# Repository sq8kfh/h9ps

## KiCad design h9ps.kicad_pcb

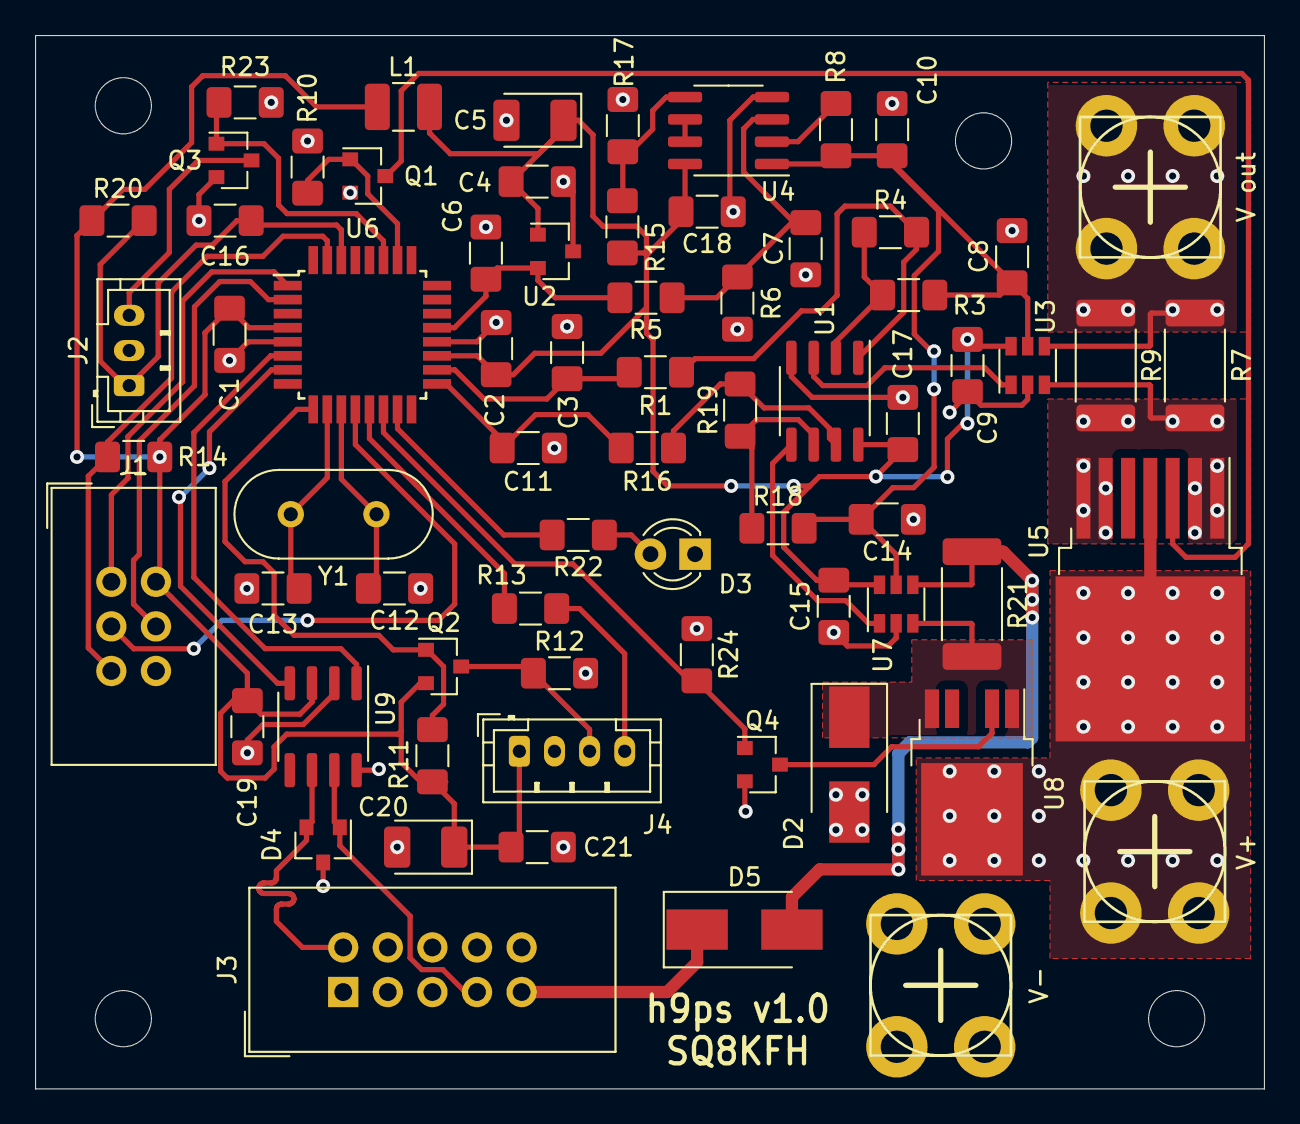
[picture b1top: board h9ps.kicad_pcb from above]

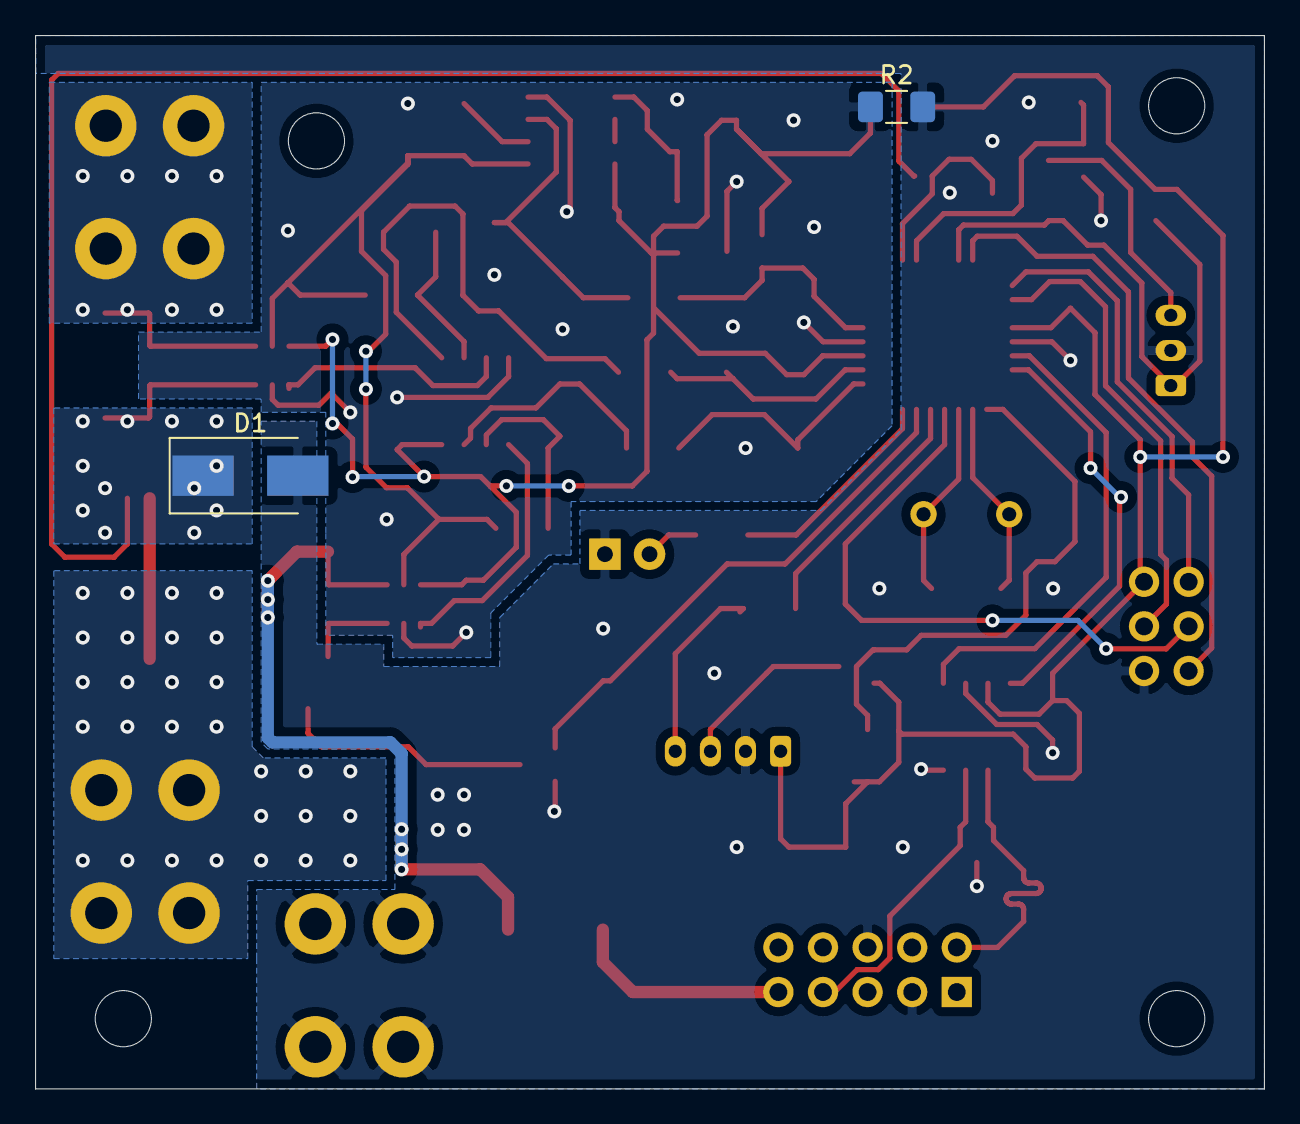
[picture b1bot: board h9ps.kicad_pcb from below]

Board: 2 copper layers, 70.0 x 60.0 mm, 73 parts (2 on the bottom side), 47 nets.

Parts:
 : MountingHole_3.2mm_M3
C1, C2, C3, C4, C7, C8, C9, C11, C14, C15, C16, C17, C18, C19, C21: 100n; C_1206_3216Metric_Pad1.42x1.75mm_HandSolder
C5, C20: 47uF; CP_EIA-3528-21_Kemet-B_Pad1.50x2.35mm_HandSolder
C6, C10: 1uF; C_1206_3216Metric_Pad1.42x1.75mm_HandSolder
C12, C13: 22p; C_1206_3216Metric_Pad1.42x1.75mm_HandSolder
D1, D2, D5: S1M; D_SMB_Handsoldering
D3: LED_Small_ALT; LED_D3.0mm
D4: NUP2105L; SOT-23
J1: AVR-ISP-6; IDC-Header_2x03_P2.54mm_Vertical
J2: Conn_01x03; JST_PH_B3B-PH-K_1x03_P2.00mm_Vertical
J3: DB9; IDC-Header_2x05_P2.54mm_Vertical
J4: Conn_01x04; JST_PH_B4B-PH-K_1x04_P2.00mm_Vertical
L1: 10uH; L_1210_3225Metric_Pad1.42x2.65mm_HandSolder
Q1, Q3, Q4: 2N7002; SOT-23
Q2: BSS84; SOT-23
R1, R13, R16: 100; R_1206_3216Metric_Pad1.42x1.75mm_HandSolder
R2, R4, R19: 0R; R_1206_3216Metric_Pad1.42x1.75mm_HandSolder
R3, R18: NN; R_1206_3216Metric_Pad1.42x1.75mm_HandSolder
R5, R6, R8, R10, R11, R12, R14, R15, R17, R20, R22, R23, R24: 10k; R_1206_3216Metric_Pad1.42x1.75mm_HandSolder
R7, R9: 0R003; R_2512_6332Metric_Pad1.52x3.35mm_HandSolder
R21: 0R3; R_2512_6332Metric_Pad1.52x3.35mm_HandSolder
U1, U4: TLC272; SOIC-8_3.9x4.9mm_P1.27mm
U2: MCP1541-TT; SOT-23
U3: INA181A3; SOT-23-6
U5: BTS50085-1TMA; TO-263-7_TabPin4
U6: ATmega16M1-AU; TQFP-32_7x7mm_P0.8mm
U7: INA181A1; SOT-23-6
U8: BTS443P; TO-252-4
U9: MCP2551-I-SN; SOIC-8_3.9x4.9mm_P1.27mm
V out: PWR_OUT; Screw_Terminal_M4
V+: VPP; Screw_Terminal_M4
V-: PWR_GND; Screw_Terminal_M4
Y1: 16MHz; Crystal_HC49-U_Vertical

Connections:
+5V: C1.1, C19.2, C20.1, C21.2, J1.2, J4.1, L1.1, Q2.2, R11.1, R14.2, R20.1, U6.4, U9.3
+5VA: C2.2, C4.2, C5.1, C9.1, C15.1, C17.2, C18.2, L1.2, R15.2, U1.8, U2.1, U3.6, U4.8, U6.19, U7.6
/-LED1: J2.3, Q3.3
/BUS_I: C11.2, R16.2, U6.17
/BUS_PWR: D5.2, R21.1, U7.4
/BUS_PWR_ON: Q4.1, R24.2, U6.14
/BUTTON: C16.2, J2.1, R20.2, U6.30
/CANH: D4.1, J3.7, U9.7
/CANL: D4.2, J3.2, U9.6
/CAN_RX: U6.7, U9.4
/CAN_TX: U6.6, U9.1
/LED1: Q3.1, R23.2, U6.27
/LED2: R22.2, U6.15
/MISO: J1.1, U6.1
/MOSI: J1.4, U6.2
/PG: J4.4, R13.2
/PS_ON: J4.3, Q2.3, R12.1
/PWR_I: C3.2, R1.2, U6.18
/PWR_ON: Q1.1, R10.2, U6.26
/RESET: J1.5, R14.1, U6.31
/SCK: J1.3, U6.12
/V_OFFSET: C8.2, C10.2, C14.2, R3.2, R8.2, R18.2, U3.5, U4.1, U7.5
GND: C1.2, C12.1, C13.1, C16.1, C19.1, C20.2, C21.1, D1.2, D2.2, D3.1, D4.3, J1.6, J2.2, J3.3, J3.6, J4.2, Q1.2, Q3.2, Q4.2, R2.2, R10.1, R12.2, R23.1, R24.1, U6.5, U9.2, U9.8, V-.1
GNDA: C2.1, C3.1, C4.1, C5.2, C6.1, C7.1, C8.1, C9.2, C10.1, C11.1, C14.1, C15.2, C17.1, C18.1, R2.1, R6.1, R17.1, U1.4, U2.3, U3.2, U4.4, U6.20, U7.2
unnamed: C6.2, R5.2, U2.2, U6.21
unnamed: C7.2, R5.1, R6.2, U4.3
unnamed: C12.2, U6.11, Y1.1
unnamed: C13.2, U6.10, Y1.2
unnamed: D1.1, R7.2, R9.2, U3.3, U5.1, U5.2, U5.6, U5.7
unnamed: D2.1, R21.2, U7.3, U8.1, U8.5
unnamed: D3.2, R22.1
unnamed: D5.1, J3.9
unnamed: R7.1, R9.1, U3.4, V out.1
unnamed: Q1.3, U5.3
unnamed: Q2.1, R11.2, U6.9
unnamed: Q4.3, U8.2
unnamed: R1.1, R4.2, U1.1
unnamed: R3.1, R4.1, U1.2
unnamed: R8.1, U4.2
unnamed: R13.1, U6.13
unnamed: R15.1, R17.2, U4.5
unnamed: R16.1, R19.2, U1.7
unnamed: R18.1, R19.1, U1.6
unnamed: U1.3, U3.1
unnamed: U1.5, U7.1
unnamed: U4.6, U4.7
VPP: U5.4, U8.3, V+.1

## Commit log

2020-01-04 init
2020-01-04 fix, v1.0
